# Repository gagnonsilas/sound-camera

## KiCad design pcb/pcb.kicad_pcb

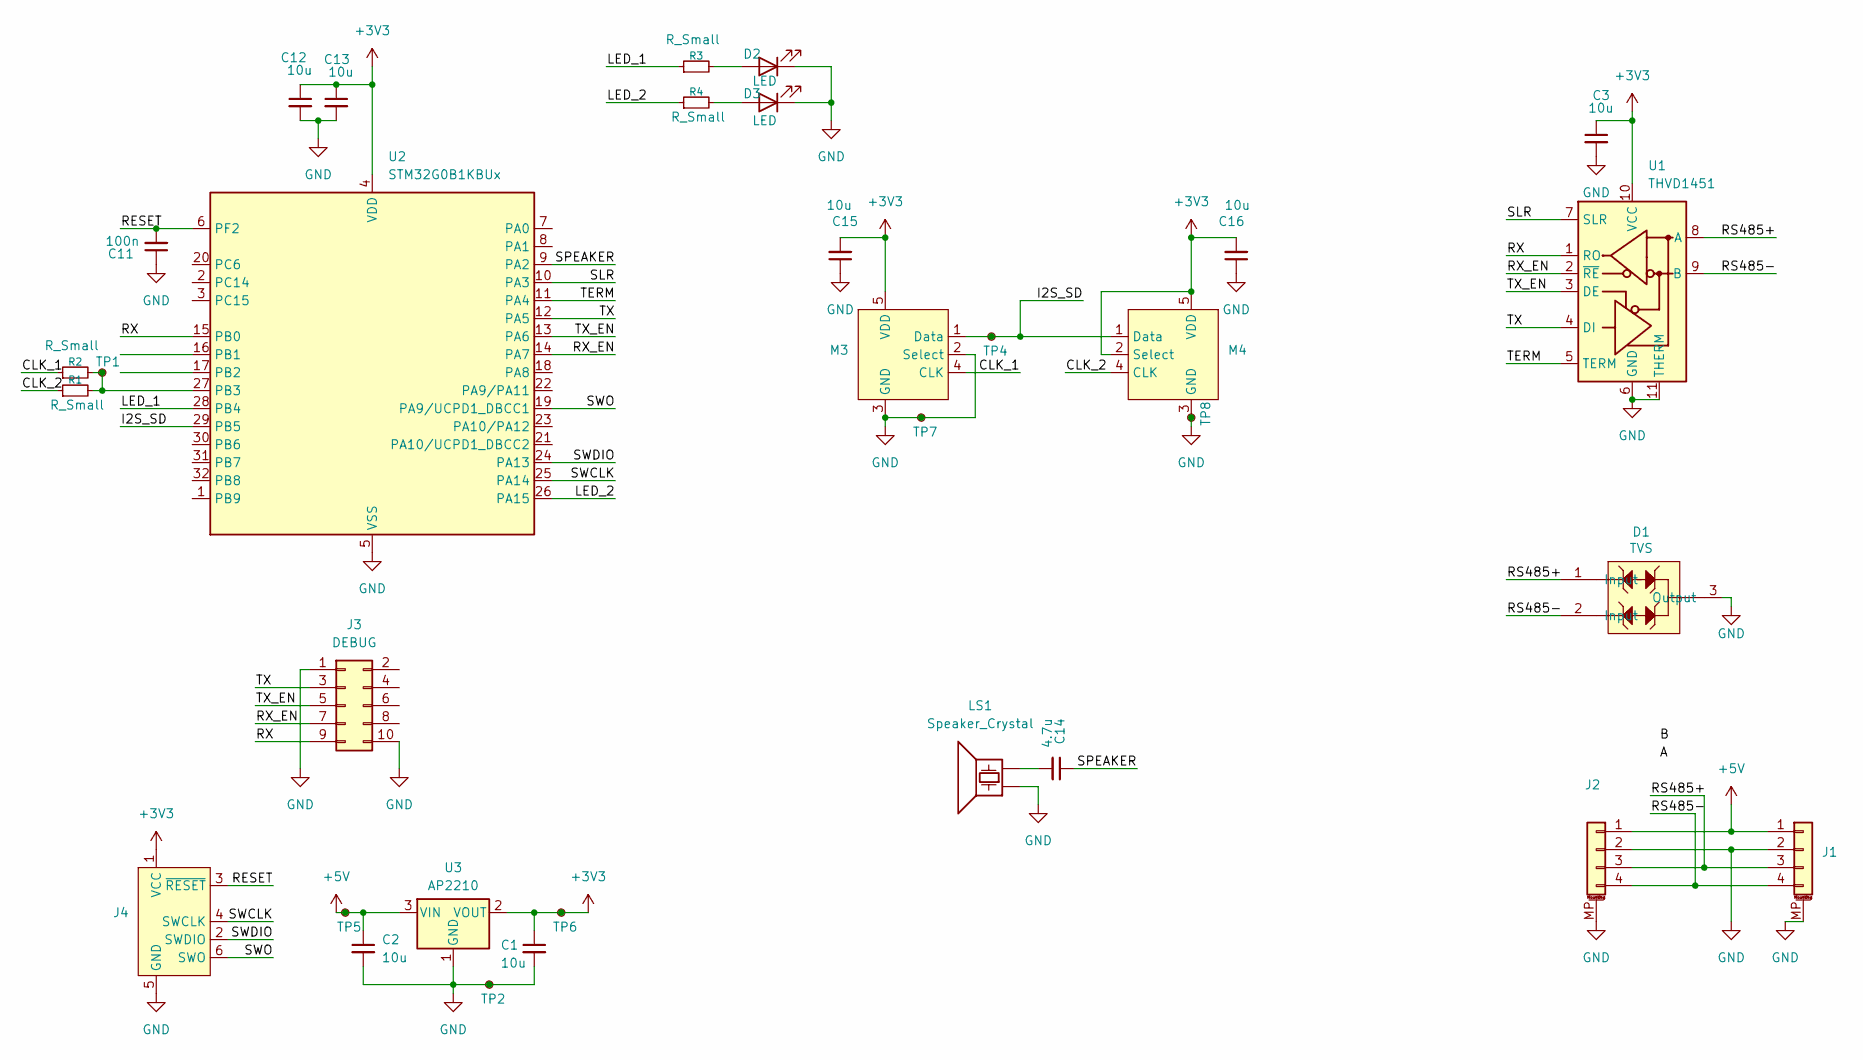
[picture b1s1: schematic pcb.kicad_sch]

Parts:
C1, C2, C13: 10u; C_0603_1608Metric
C3, C12, C15, C16: 10u; C_0402_1005Metric
C11: 100n; C_0402_1005Metric
C14: 4.7u; C_0603_1608Metric
D1: TVS; SOT-23-3; LCSC C32677
D2, D3: LED; D_0402_1005Metric
J1, J2: Conn_01x04_MountingPin; CONN04_5055670471_MOL
J3: DEBUG; PinHeader_2x05_P1.27mm_Vertical_SMD
J4: Conn_ARM_SWD_TagConnect_TC2030-NL; Tag-Connect_TC2030-IDC-NL_2x03_P1.27mm_Vertical
LS1: Speaker_Crystal; PKMCS0909E4000-R1
M3, M4: T3902
R1, R2, R3, R4: R_Small; R_0402_1005Metric
TP1: CLK; tp-ev24
TP2, TP7, TP8: GND; tp-ev24
TP4: SD; tp-ev24
TP5: 5V; tp-ev24
TP6: 3V3; tp-ev24
U1: THVD1451; VSON-10-1EP_3x3mm_P0.5mm_EP1.65x2.4mm_ThermalVias
U2: STM32G0B1KBUx; QFN-32-1EP_5x5mm_P0.5mm_EP3.45x3.45mm
U3: AP2210; SOT-23-3

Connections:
+3V3: C1.1, C3.1, C12.1, C13.1, C15.2, C16.2, J4.1 (VCC), M3.5 (VDD), M4.2 (Select), M4.5 (VDD), TP6.1, U1.10 (VCC), U2.4 (VDD), U3.2 (VOUT)
+5V: C2.1, J1.1, J2.1, TP5.1, U3.3 (VIN)
/CLK_1: M3.4 (CLK), R2.1
/CLK_2: M4.4 (CLK), R1.1
/I2S_SD: M3.1 (Data), M4.1 (Data), TP4.1, U2.29 (PB5)
/LED_1: R3.1, U2.28 (PB4)
/LED_2: R4.1, U2.26 (PA15)
/RESET: C11.2, J4.3 (~RESET), U2.6 (PF2)
/RS485+: D1.1 (Input), J1.3, J2.3, U1.8 (A)
/RS485-: D1.2 (Input), J1.4, J2.4, U1.9 (B)
/RX: J3.9, U1.1 (RO), U2.15 (PB0)
/RX_EN: J3.7, U1.2 (~RE), U2.14 (PA7)
/SLR: U1.7 (SLR), U2.10 (PA3)
/SPEAKER: C14.1, U2.9 (PA2)
/SWCLK: J4.4 (SWCLK), U2.25 (PA14)
/SWDIO: J4.2 (SWDIO), U2.24 (PA13)
/SWO: J4.6 (SWO), U2.19 (PA9/UCPD1_DBCC1)
/TERM: U1.5 (TERM), U2.11 (PA4)
/TX: J3.3, U1.4 (DI), U2.12 (PA5)
/TX_EN: J3.5, U1.3 (DE), U2.13 (PA6)
GND: C1.2, C2.2, C3.2, C11.1, C12.2, C13.2, C15.1, C16.1, D1.3 (Output), D2.1 (K), D3.1 (K), J1.2, J1.MP (MountPin), J2.2, J2.MP (MountPin), J3.1, J3.10, J4.5 (GND), LS1.1, M3.2 (Select), M3.3 (GND), M4.3 (GND), TP2.1, TP7.1, TP8.1, U1.6 (GND), U1.11 (THERM), U2.5 (VSS), U2.33 (VSS), U3.1 (GND)
unnamed: C14.2, LS1.2
unnamed: D2.2 (A), R3.2
unnamed: D3.2 (A), R4.2
unnamed: R1.2, R2.2, TP1.1, U2.27 (PB3)

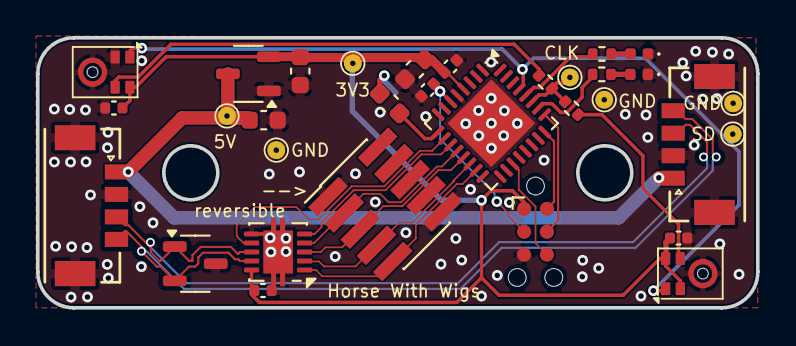
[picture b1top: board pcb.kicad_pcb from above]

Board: 4 copper layers, 40.0 x 15.0 mm, 33 parts (1 on the bottom side), 25 nets.

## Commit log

2025-05-23 schematic?
2025-05-24 unrouted nets 0
2025-05-24 more vias
2025-05-27 improve routing
2025-05-28 re route!!!
2025-05-28 routed with STM mic
2025-05-28 T3902 Mic
2025-06-09 pcb fixes
2025-06-09 implement dumb sim
2025-06-30 Fixed flake on Mac
2025-06-30 add source termination
2025-07-01 fix drc
2025-08-23 add rs485
2025-08-24 rs485 re route
2025-08-24 small tweaks
2025-08-25 silkscreen
